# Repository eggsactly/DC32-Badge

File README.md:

# About 
The DEFCON 32 CPEC badge design, done in kicad 6. Repo contains both a schematic and PCB design. 

This design uses the pervasive displays E2266QS0F1 E-Ink display; https://www.pervasivedisplays.com/product/2-66-e-ink-displays/

## Goal (functional requirements)
Design of the final board will do these functions. Many of them will be implemented in embedded software, which the board hardware will enable. 

- When the user attaches a lanyard to the two holes cut into the top of the board, the user will be able to wear this board around their neck. 
- When the user turns on the board, the board will read the contents of the SD card, and will display the first BMP file on the e-ink display.
- When the user pushes the image select button, SW4, the board will display the next BMP on the SD card.
- When the user plugs in an SAO board to J3, J4, or J5, the board will supply 3.3v DC power to the SAO board. 
- Board will be programmed over UART with a FTDI cable. When the developer switches SW5 to program, plugs a FTDI cable into J1, and presses SW3 to reset the board, the developer will load their ESP32 image over the serial bus. 
- When the user switches switch SW2 to "Be Evil" the board will do something mischievous. 
- LEDs will blink in a cool pattern. 

# Questions/Risks  (non-functional requirements)
This section covers specific questions and possible risks, which may lead to non-functional requirements on the design. 

## Specific Questions
- Can the ESP32-S2-WROOM-1 "EN" in be used as a Chip Pullup?
- Can the ESP32-S2-WROOM-1 "GPIO2" be used as a SPI Data Out pin?
- Can the ESP32-S2-WROOM-1 "GPIO3" be used as a SPI Chip Select pin? 
- Can the ESP32-S2-WROOM-1 "GPIO6" be used as a SPI Clock pin? 
- Can the ESP32-S2-WROOM-1 "GPIO7" be used as a SPI Data In pin? 

## Risks
- The SPI clock line is longer than the data line on the PCB layout. This may lead to a drift in the SPI clock from the data. May lead to an inability to use the Display or SD card. 
- Something about this design may be non-manufacturable 
  - Are vias too close to lines? 
  - Are there too many vias? 
  - Are some lines too close to the edge? 
  - Are some lines too close together? 
  - Are some pads too small? 

# Details 

Kicad version
```
Application: KiCad

Version: 6.0.11+dfsg-1, release build

Libraries:
	wxWidgets 3.2.2
	libcurl/7.88.1 OpenSSL/3.0.11 zlib/1.2.13 brotli/1.0.9 zstd/1.5.4 libidn2/2.3.3 libpsl/0.21.2 (+libidn2/2.3.3) libssh2/1.10.0 nghttp2/1.52.0 librtmp/2.3 OpenLDAP/2.5.13

Platform: Linux 6.1.0-18-amd64 x86_64, 64 bit, Little endian, wxGTK, gnome, wayland

Build Info:
	Date: Jan 26 2023 05:35:43
	wxWidgets: 3.2.1 (wchar_t,wx containers) GTK+ 3.24
	Boost: 1.74.0
	OCC: 7.6.3
	Curl: 7.87.0
	ngspice: 38
	Compiler: GCC 12.2.0 with C++ ABI 1017

Build settings:
	KICAD_USE_OCC=ON
	KICAD_SPICE=ON
```

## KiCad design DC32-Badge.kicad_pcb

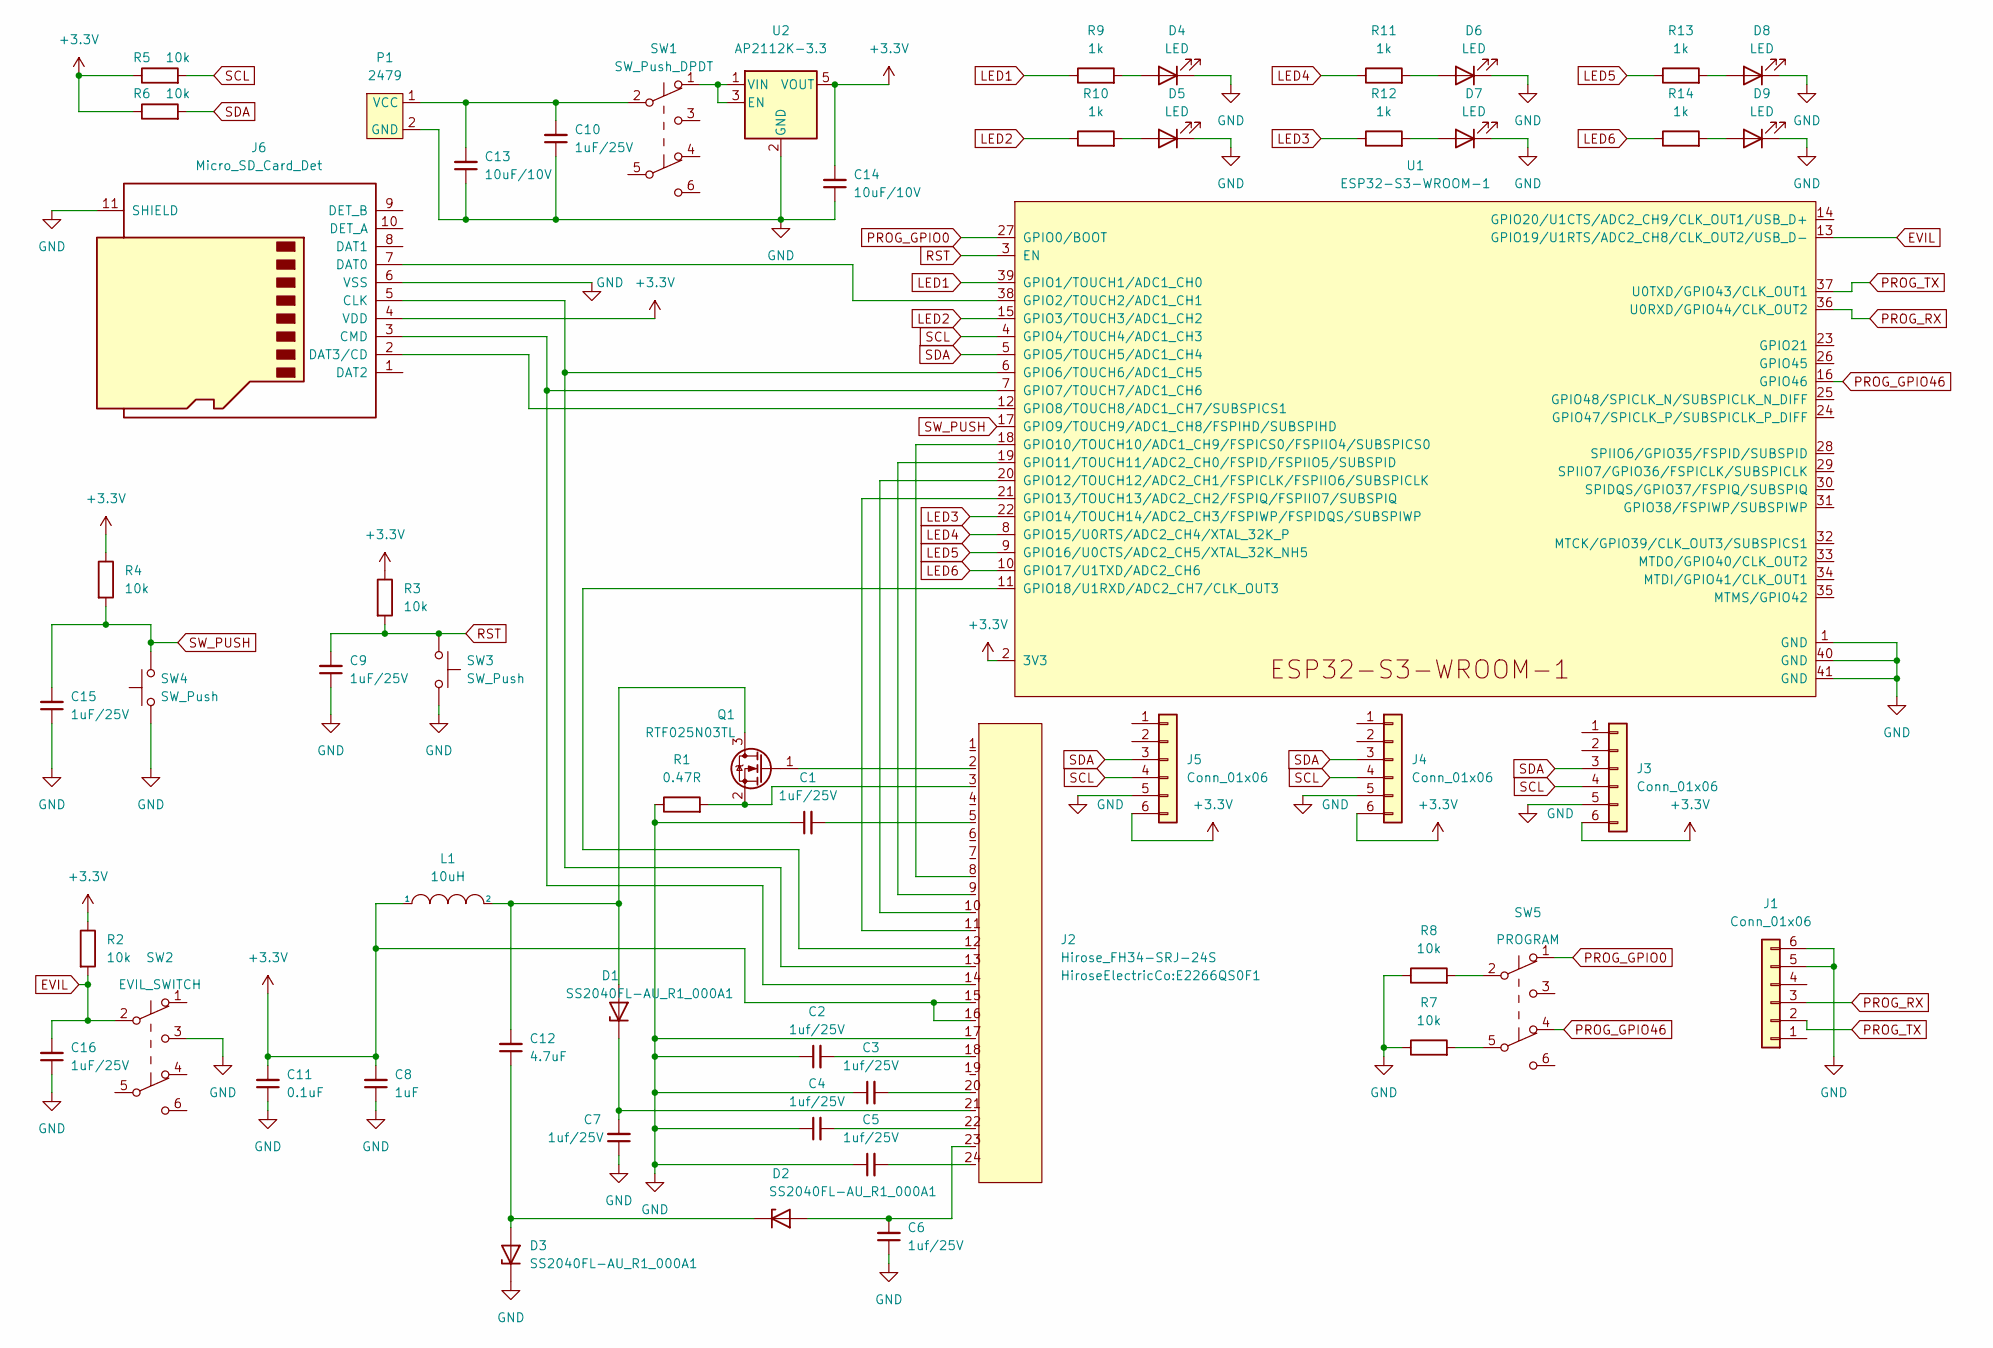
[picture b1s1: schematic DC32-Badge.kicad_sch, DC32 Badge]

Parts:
C1, C9, C10, C15, C16: 1uF/25V; C_0603_1608Metric
C2, C3, C4, C5, C6, C7: 1uf/25V; C_0603_1608Metric
C8: 1uF; C_0603_1608Metric
C11: 0.1uF; C_0402_1005Metric
C12: 4.7uF; C_0805_2012Metric
C13, C14: 10uF/10V; C_0805_2012Metric
D1, D2, D3: SS2040FL-AU_R1_000A1; D_SOD-123F
D4, D5, D6, D7, D8, D9: LED; LED_0201_0603Metric
J1: Conn_01x06; PinSocket_1x06_P2.54mm_Vertical_SMD_Pin1Left
J2: Hirose_FH34-SRJ-24S; E2266QS0F1
J3, J4, J5: Conn_01x06; PinHeader_2x03_P2.54mm_Vertical
J6: Micro_SD_Card_Det; microSD_HC_Hirose_DM3AT-SF-PEJM5
L1: 10uH; L_0805_2012Metric
P1: 2479; BatteryHolder_Keystone_2479_3xAAA
Q1: RTF025N03TL; SOT-323_SC-70
R1: 0.47R; R_0603_1608Metric
R2, R3, R4, R5, R6, R7, R8: 10k; R_0603_1608Metric
R9, R10, R11, R12, R13, R14: 1k; R_0603_1608Metric
SW1: SW_Push_DPDT; SW_E-Switch_EG1271_SPDT
SW2: EVIL_SWITCH; SW_E-Switch_EG1271_SPDT
SW3, SW4: SW_Push; SW_SPST_B3S-1000
SW5: PROGRAM; SW_E-Switch_EG1271_SPDT
U1: ESP32-S3-WROOM-1
U2: AP2112K-3.3; SOT-23-5

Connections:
+3.3V: C8.2, C11.2, C14.2, J2.15, J2.16, J3.6, J4.6, J5.6, J6.4 (VDD), L1.1, R2.1, R3.1, R4.1, R5.1, R6.1, U1.2 (3V3), U2.5 (VOUT)
EVIL: C16.2, R2.2, SW2.2 (B), U1.13 (GPIO19/U1RTS/ADC2_CH8/CLK_OUT2/USB_D-)
GND: C1.1, C2.1, C3.1, C4.1, C5.1, C6.1, C7.1, C8.1, C9.1, C10.1, C11.1, C13.1, C14.1, C15.1, C16.1, D3.1 (K), D4.1 (K), D5.1 (K), D6.1 (K), D7.1 (K), D8.1 (K), D9.1 (K), J1.5, J1.6, J2.17, J3.5, J4.5, J5.5, J6.6 (VSS), J6.11 (SHIELD), P1.2 (GND), R1.1, R7.1, R8.1, SW2.3 (C), SW3.2, SW4.1, U1.1 (GND), U1.40 (GND), U1.41 (GND), U2.2 (GND)
LED1: R9.1, U1.39 (GPIO1/TOUCH1/ADC1_CH0)
LED2: R10.1, U1.15 (GPIO3/TOUCH3/ADC1_CH2)
LED3: R12.1, U1.22 (GPIO14/TOUCH14/ADC2_CH3/FSPIWP/FSPIDQS/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)
LED4: R11.1, U1.8 (GPIO15/U0RTS/ADC2_CH4/XTAL_32K_P)
LED5: R13.1, U1.9 (GPIO16/U0CTS/ADC2_CH5/XTAL_32K_NH5)
LED6: R14.1, U1.10 (GPIO17/U1TXD/ADC2_CH6)
unnamed: C1.2, J2.5
unnamed: C2.2, J2.18
unnamed: C3.2, J2.20
unnamed: C4.2, J2.22
unnamed: C5.2, J2.24
unnamed: C6.2, D2.2 (A), J2.23
unnamed: C7.2, D1.1 (K), J2.21
unnamed: C10.2, C13.2, P1.1 (VCC), SW1.2 (B)
unnamed: C12.1, D2.1 (K), D3.2 (A)
unnamed: C12.2, D1.2 (A), L1.2, Q1.3 (D)
unnamed: D4.2 (A), R9.2
unnamed: D5.2 (A), R10.2
unnamed: D6.2 (A), R11.2
unnamed: D7.2 (A), R12.2
unnamed: D8.2 (A), R13.2
unnamed: D9.2 (A), R14.2
unnamed: J2.2, Q1.1 (G)
unnamed: J2.3, Q1.2 (S), R1.2
unnamed: J2.8, U1.18 (GPIO10/TOUCH10/ADC1_CH9/FSPICS0/FSPIIO4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)
unnamed: J2.9, U1.19 (GPIO11/TOUCH11/ADC2_CH0/FSPID/FSPIIO5/S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)
unnamed: J2.10, U1.20 (GPIO12/TOUCH12/ADC2_CH1/FSPICLK/FSPIIO6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)
unnamed: J2.11, U1.21 (GPIO13/TOUCH13/ADC2_CH2/FSPIQ/FSPIIO7/S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)
unnamed: J2.12, U1.11 (GPIO18/U1RXD/ADC2_CH7/CLK_OUT3)
unnamed: J2.13, J6.5 (CLK), U1.6 (GPIO6/TOUCH6/ADC1_CH5)
unnamed: J2.14, J6.3 (CMD), U1.7 (GPIO7/TOUCH7/ADC1_CH6)
unnamed: J6.2 (DAT3/CD), U1.12 (GPIO8/TOUCH8/ADC1_CH7/SUBSPICS1)
unnamed: J6.7 (DAT0), U1.38 (GPIO2/TOUCH2/ADC1_CH1)
unnamed: R7.2, SW5.5 (B)
unnamed: R8.2, SW5.2 (B)
unnamed: SW1.1 (A), U2.1 (VIN), U2.3 (EN)
PROG_GPIO0: SW5.1 (A), U1.27 (GPIO0/BOOT)
PROG_GPIO46: SW5.4 (A), U1.16 (GPIO46)
PROG_RX: J1.3, U1.36 (U0RXD/GPIO44/CLK_OUT2)
PROG_TX: J1.2, U1.37 (U0TXD/GPIO43/CLK_OUT1)
RST: C9.2, R3.2, SW3.1, U1.3 (EN)
SCL: J3.4, J4.4, J5.4, R5.2, U1.4 (GPIO4/TOUCH4/ADC1_CH3)
SDA: J3.3, J4.3, J5.3, R6.2, U1.5 (GPIO5/TOUCH5/ADC1_CH4)
SW_PUSH: C15.2, R4.2, SW4.2, U1.17 (GPIO9/TOUCH9/ADC1_CH8/FSPIHD/SUBSPIHD)

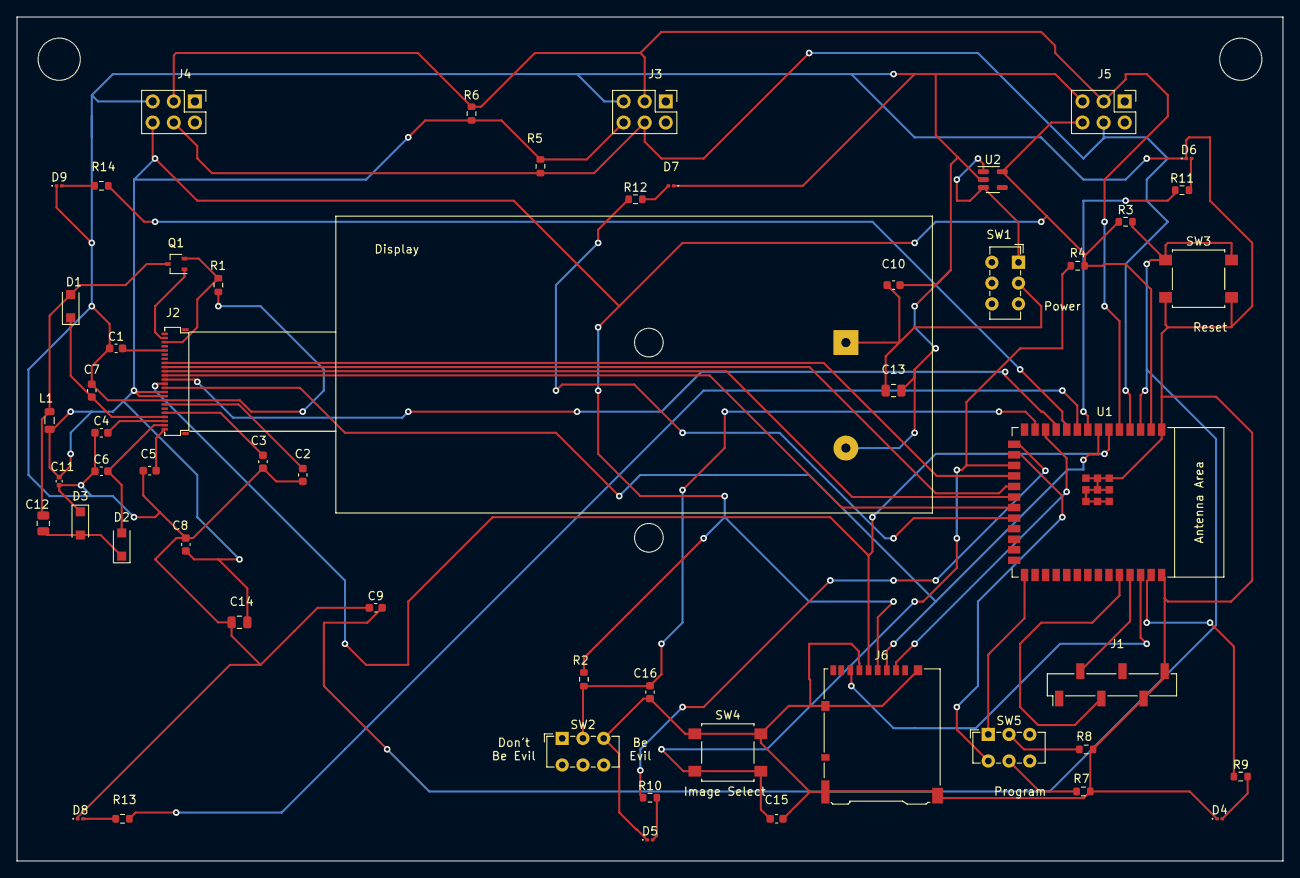
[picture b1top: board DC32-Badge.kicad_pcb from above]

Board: 2 copper layers, 152.4 x 101.6 mm, 55 parts (1 on the bottom side), 47 nets.

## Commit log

2024-04-01 Initial commit.
2024-04-01 Added libraries as submodules.
2024-04-01 Made relative paths work in fp-lib-table and sym-lib-table.
2024-04-01 Replaced ESP32-MINI with ESP32-WROOM in the kicad_sch file.
2024-04-01 Added Questions.txt.
2024-04-01 Added ignore for strange auto_saved_files file.
2024-04-02 Fit design on one page by modularizon. Added some button debouncing capacitors. Changed some of the GPIO pins.
2024-04-02 Added third SAO port.
2024-04-02 Rearranged some pins. Added a PROGRAM switch.
2024-04-02 Ran electrical rules checker.
2024-04-02 Added 6 LEDs
2024-04-02 Initial place and route.
2024-04-02 Adjustments prior to route.
2024-04-02 Removed pinned libraries from project.
2024-04-02 Cleaned up unused libraries.
2024-04-02 Changed SAO board footprint to a throughhole footprint.
2024-04-02 Updated footprint library in schematic editor. Rearranged some componets on the PCB editor.
2024-04-05 Initial route.
2024-04-07 Updated placing and routing for power capacitors.
2024-04-07 Updated submodule to point to internet path.
2024-04-09 Updated silkscreen.
2024-04-09 Added README.
